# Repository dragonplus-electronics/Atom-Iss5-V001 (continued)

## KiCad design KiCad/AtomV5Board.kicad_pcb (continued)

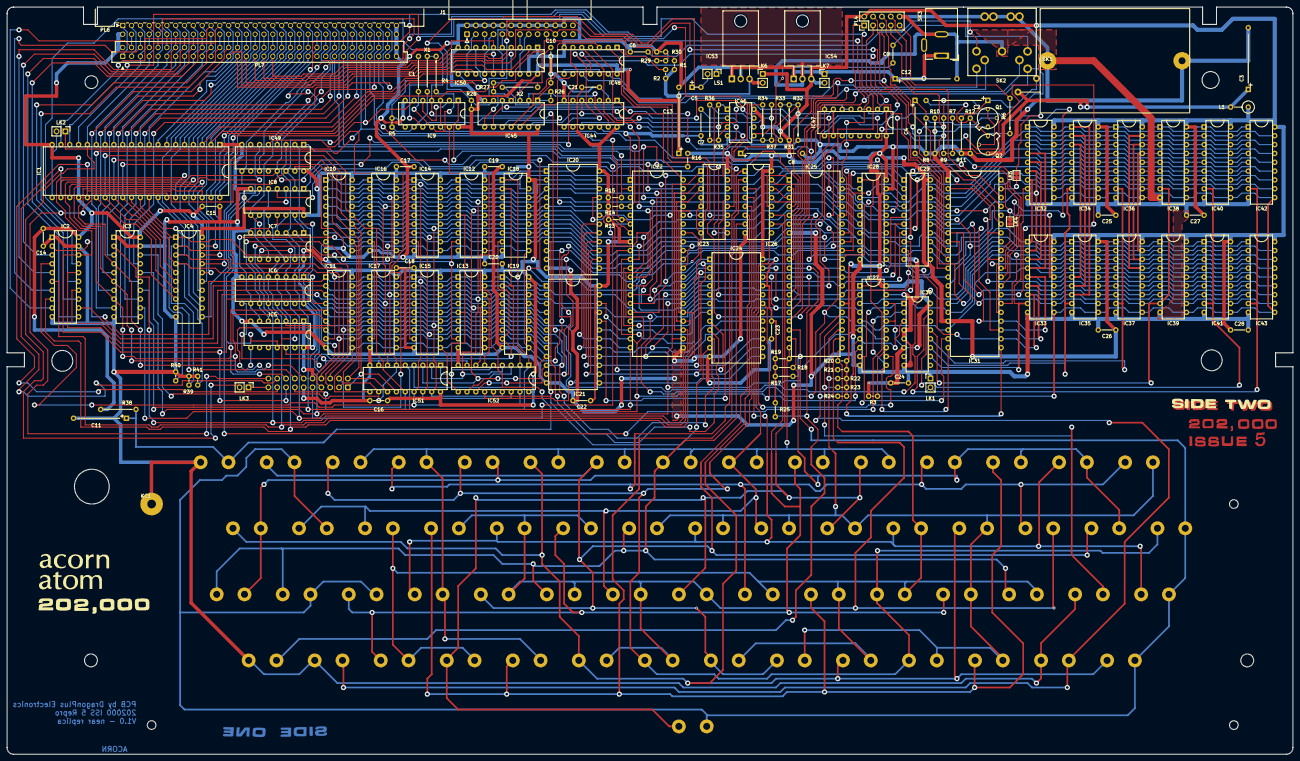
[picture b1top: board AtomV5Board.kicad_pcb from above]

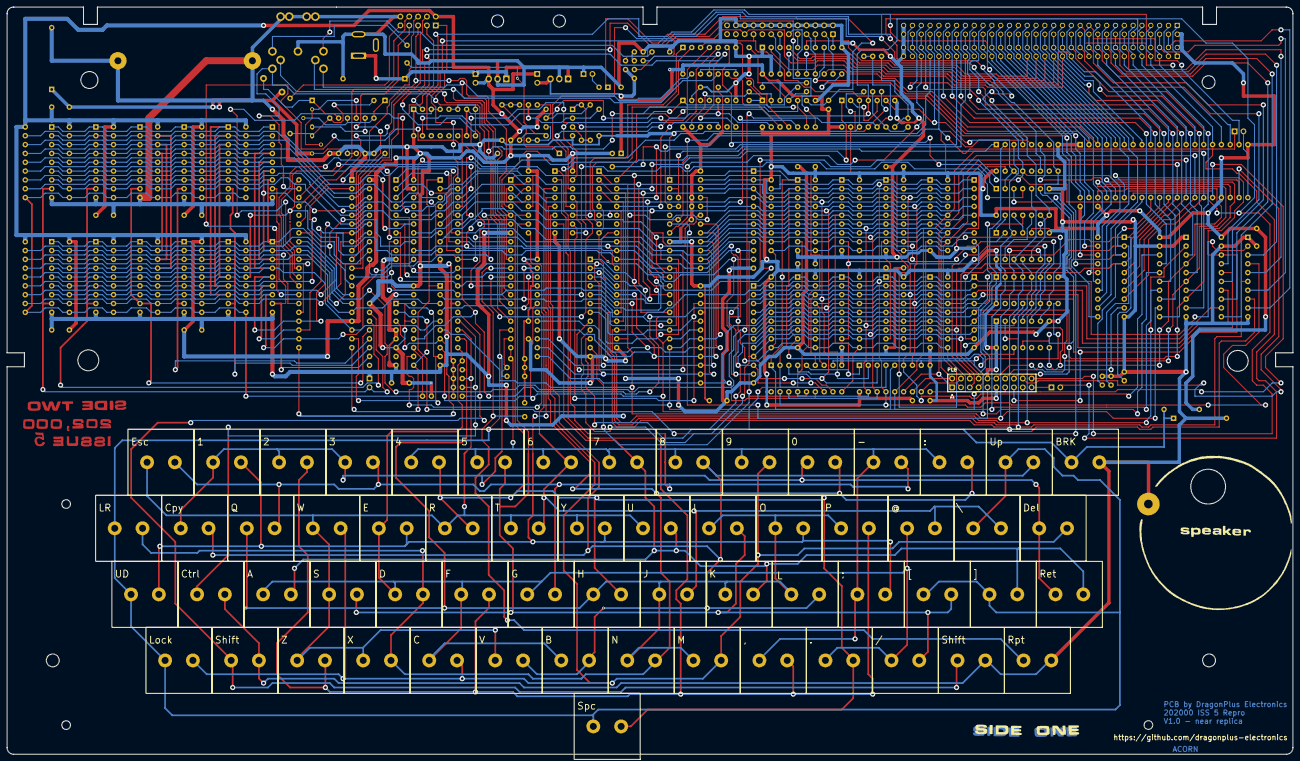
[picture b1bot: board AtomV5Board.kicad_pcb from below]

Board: 2 copper layers, 370.0 x 215.0 mm, 207 parts (63 on the bottom side), 230 nets.

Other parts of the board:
G002a: LOGO; SIDE_ONE
G002b: LOGO; SIDE_ONE_F_cu
KC1: KeybdChasGnd; KeyboardGround

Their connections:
GND: KC1.1; also elsewhere on the board

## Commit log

2024-11-30 Initial commit
    Initial commit
2024-11-30 Add KiCad Files
2024-11-30 Update Gerbers
2024-11-30 Update license and readme.
